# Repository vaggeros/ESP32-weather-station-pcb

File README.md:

# ESP32 - Weather Station PCB

Simple PCB with through hole components which can integrate easily environmental sensors (bme320,sht40) and implement a simple weather station . The initial design was based on ESP-32 Dev Kit . The PCB is supplied through the USB port of the ESP-32 Dev Kit.

## Project structure

- **Gerbers**

  Here can be found the Gerbers of the PCB in order to manufacture the above PCB

-  **Doc**

​		Here can be found a **PNG** image of the PCB and the **STEP** file.

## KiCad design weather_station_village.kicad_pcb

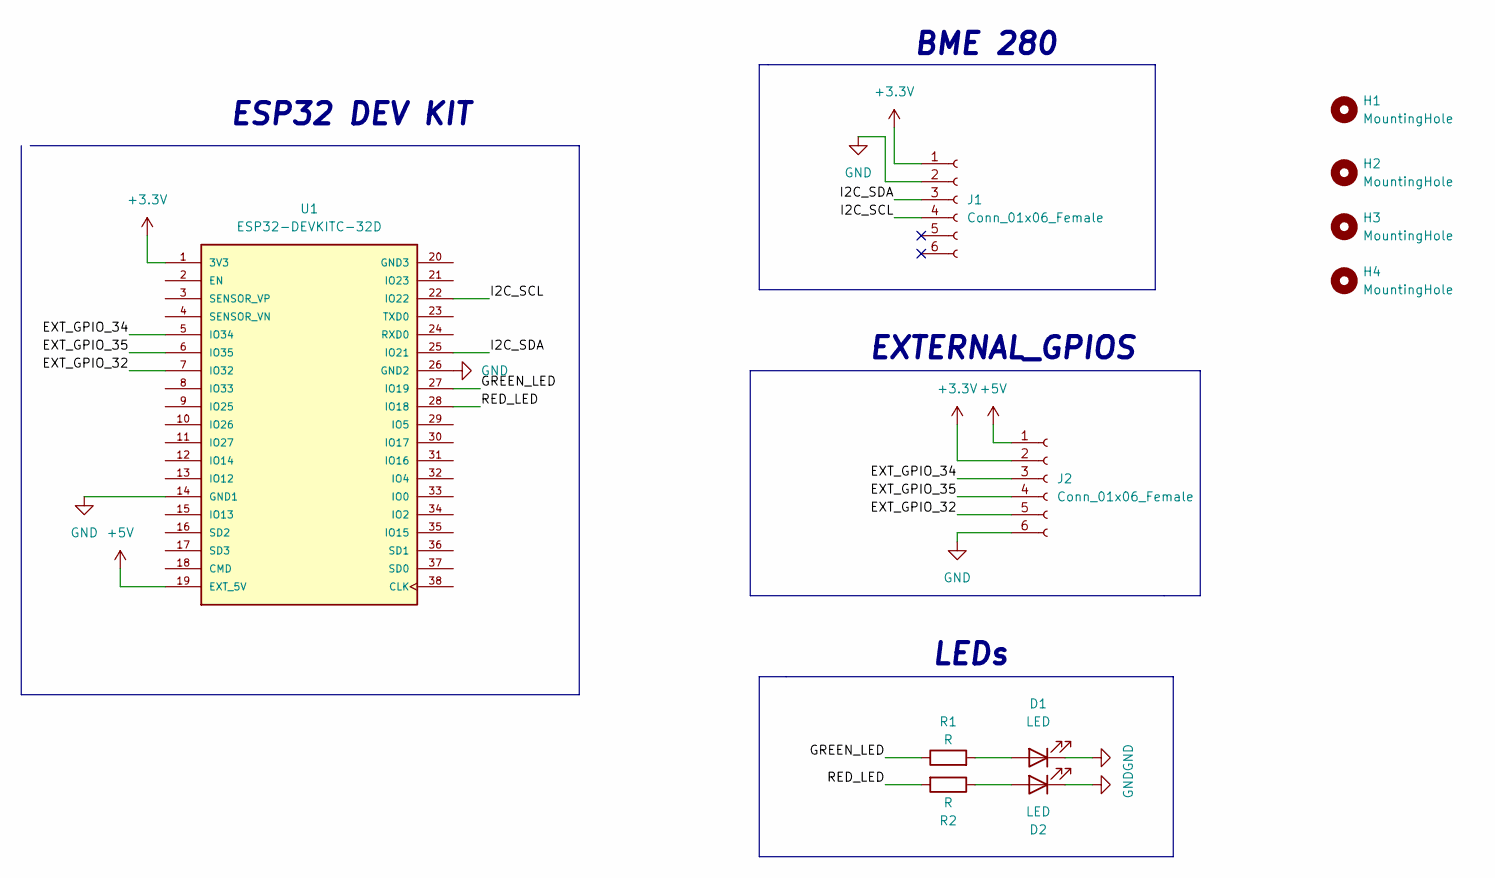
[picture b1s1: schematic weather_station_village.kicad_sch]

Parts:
D1, D2: LED; LED_D3.0mm
H1, H2, H3, H4: MountingHole; MountingHole_2mm
J1, J2: Conn_01x06_Female; PinHeader_1x06_P2.54mm_Vertical
R1, R2: R; R_Axial_DIN0204_L3.6mm_D1.6mm_P5.08mm_Horizontal
U1: ESP32-DEVKITC-32D; MODULE_ESP32-DEVKITC-32D; PARTREV 4

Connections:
+3.3V: J1.1, J2.2, U1.1 (3V3)
+5V: J2.1, U1.19 (EXT_5V)
/EXT_GPIO_32: J2.5, U1.7 (IO32)
/EXT_GPIO_34: J2.3, U1.5 (IO34)
/EXT_GPIO_35: J2.4, U1.6 (IO35)
/GREEN_LED: R1.1, U1.27 (IO19)
/I2C_SCL: J1.4, U1.22 (IO22)
/I2C_SDA: J1.3, U1.25 (IO21)
/RED_LED: R2.2, U1.28 (IO18)
GND: D1.1 (K), D2.1 (K), J1.2, J2.6, U1.14 (GND1), U1.26 (GND2)
unnamed: D1.2 (A), R1.2
unnamed: D2.2 (A), R2.1

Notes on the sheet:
BME 280
EXTERNAL_GPIOS
ESP32 DEV KIT
LEDs

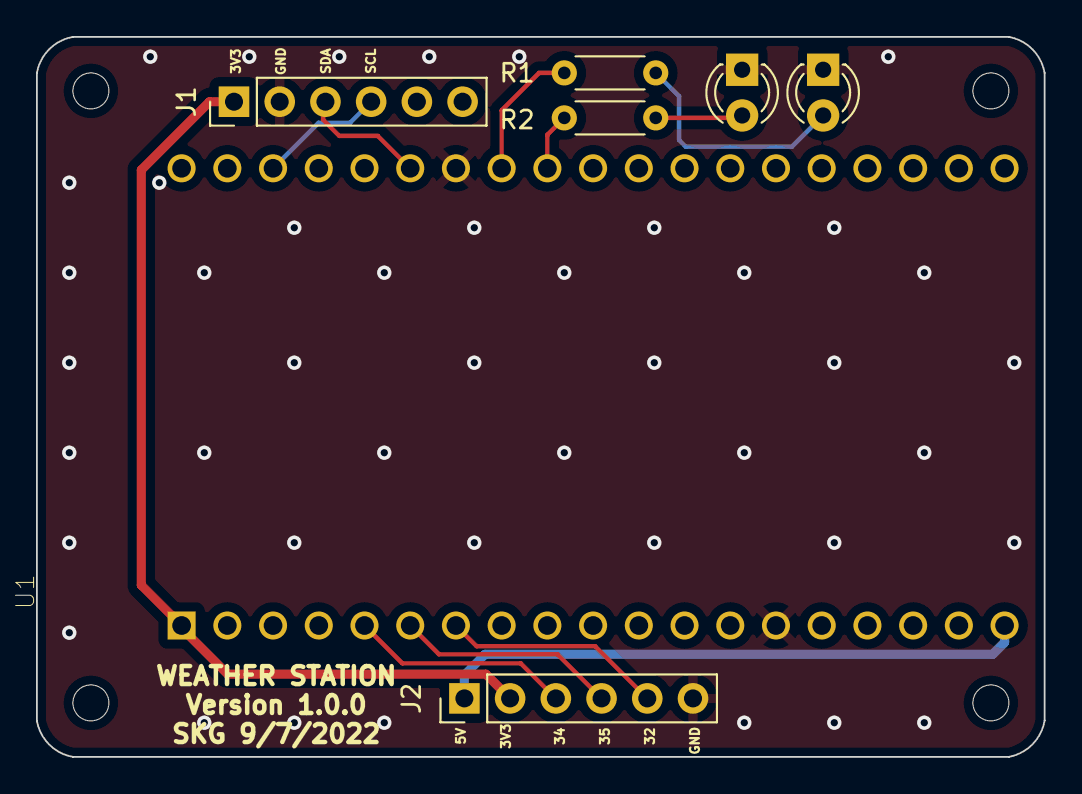
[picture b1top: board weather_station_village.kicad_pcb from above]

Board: 2 copper layers, 56.0 x 40.0 mm, 11 parts (0 on the bottom side), 12 nets.

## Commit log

2022-08-25 Added gitignore and Updated Readme
